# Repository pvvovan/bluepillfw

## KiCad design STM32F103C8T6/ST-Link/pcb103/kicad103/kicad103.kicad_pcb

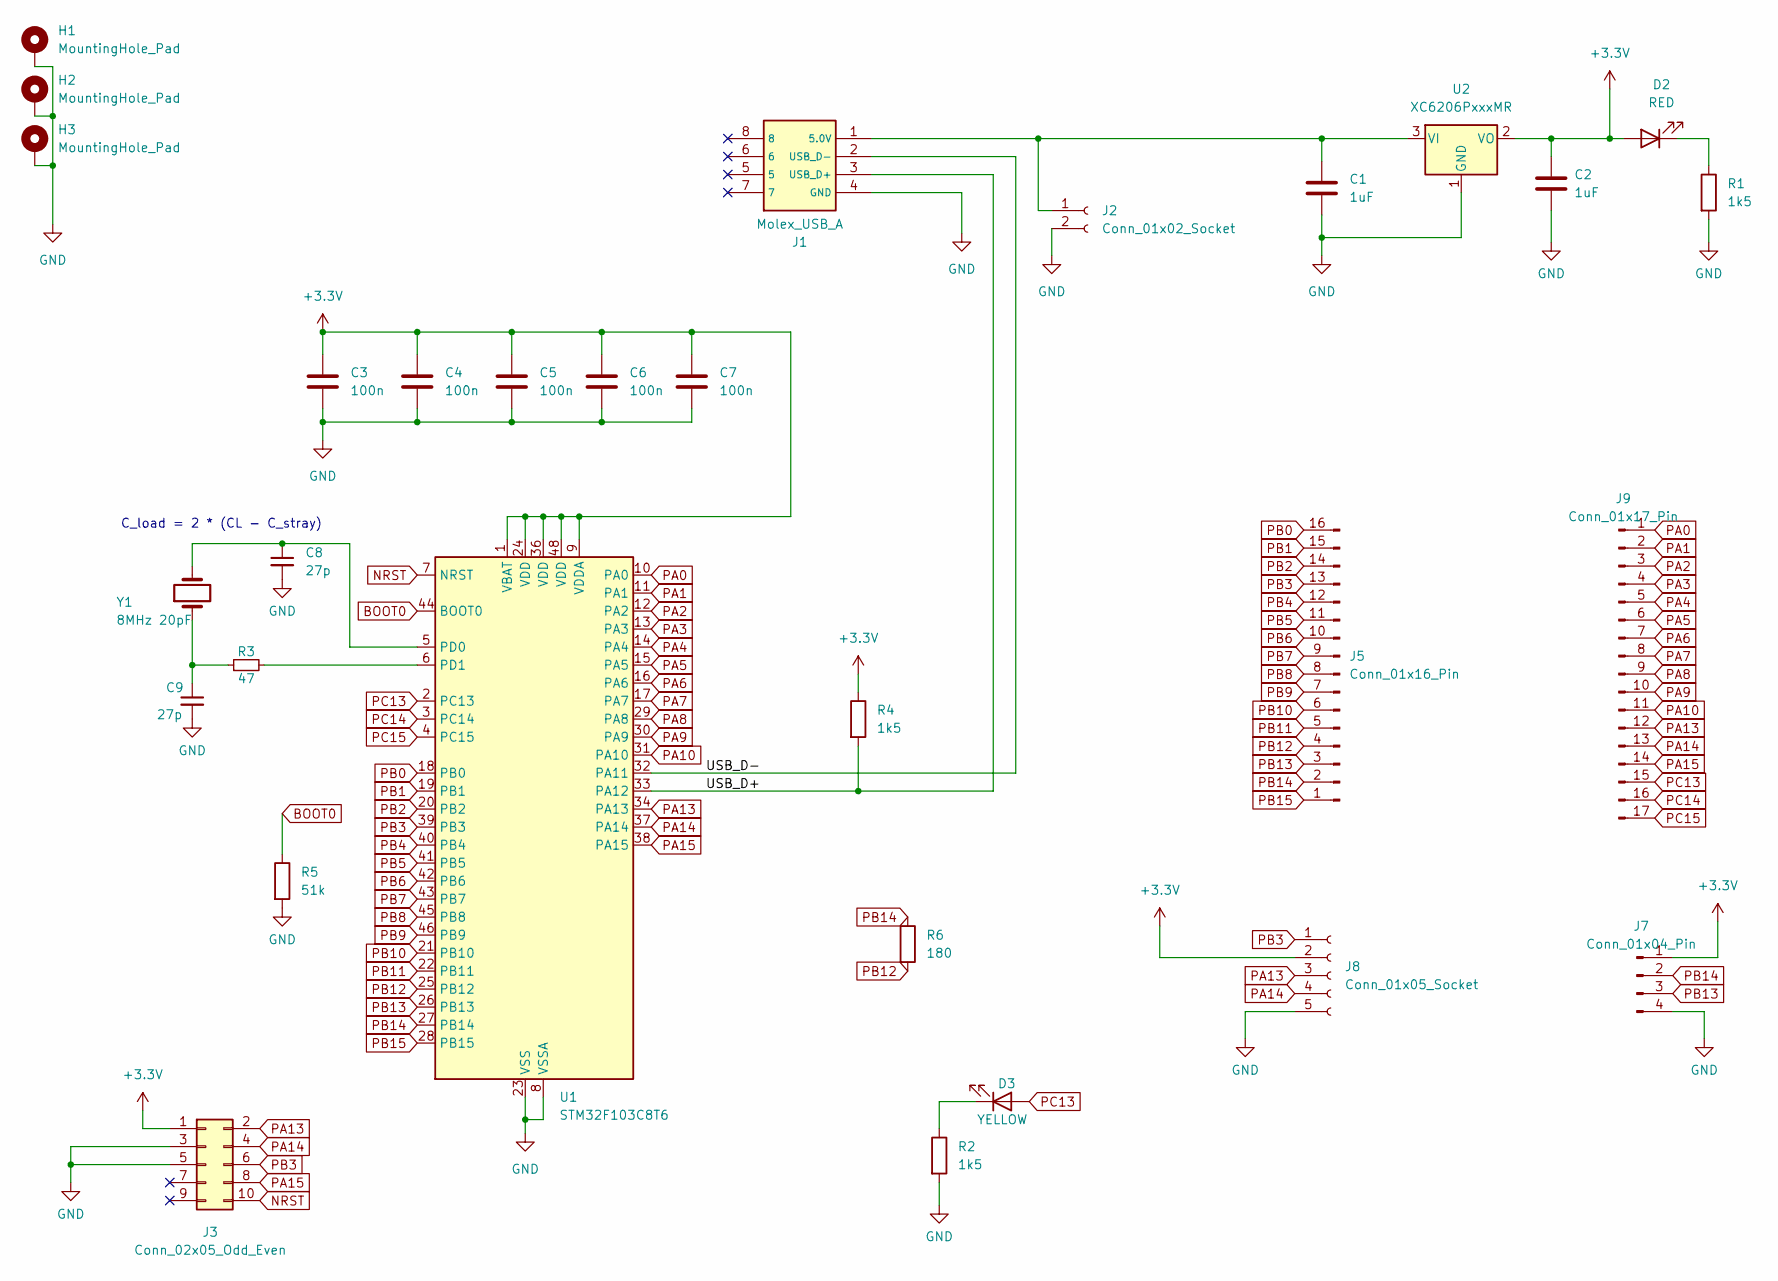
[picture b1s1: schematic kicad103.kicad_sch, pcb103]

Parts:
C1, C2: 1uF; C_0805_2012Metric; JLC # C28323
C3, C4, C5, C6, C7: 100n; C_0603_1608Metric; JLC # C14663
C8, C9: 27p; C_0402_1005Metric; JLC # C1557
D2: RED; LED_0805_2012Metric; JLC # C84256
D3: YELLOW; LED_0805_2012Metric; JLC # C2296
H1, H2, H3: MountingHole_Pad; MountingHole_4.3mm_M4_Pad_Via
J1: Molex_USB_A; Manufacturer_Part_Number 0480372200; Mouser Part Number N/A
J2: Conn_01x02_Socket; PinSocket_1x02_P2.54mm_Vertical
J3: Conn_02x05_Odd_Even; PinHeader_2x05_P1.27mm_Vertical_SMD; JLC # C2881910
J5: Conn_01x16_Pin; PinHeader_1x16_P2.54mm_Vertical
J7: Conn_01x04_Pin; PinSocket_1x04_P2.54mm_Vertical
J8: Conn_01x05_Socket; PinSocket_1x05_P2.54mm_Vertical
J9: Conn_01x17_Pin; PinHeader_1x17_P2.54mm_Vertical
R1, R2, R4: 1k5; R_0805_2012Metric; JLC # C4310
R3: 47; R_0402_1005Metric; JLC # C25118
R5: 51k; R_0805_2012Metric; JLC # C17737
R6: 180; R_1206_3216Metric; JLC # C17924
U1: STM32F103C8T6; LQFP-48_7x7mm_P0.5mm; JLC # C8734
U2: XC6206PxxxMR; SOT-23-3; JLC # C5446
Y1: 8MHz 20pF; Crystal_SMD_5032-2Pin_5.0x3.2mm; JLC # C115962

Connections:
+3.3V: C2.1, C3.1, C4.1, C5.1, C6.1, C7.1, D2.2 (A), J3.1, J7.1, J8.2, R4.1, U1.1 (VBAT), U1.9 (VDDA), U1.24 (VDD), U1.36 (VDD), U1.48 (VDD), U2.2 (VO)
/USB_D+: J1.3 (USB_D+), R4.2, U1.33 (PA12)
/USB_D-: J1.2 (USB_D-), U1.32 (PA11)
BOOT0: R5.1, U1.44 (BOOT0)
GND: C1.2, C2.2, C3.2, C4.2, C5.2, C6.2, C7.2, C8.2, C9.2, H1.1, H2.1, H3.1, J1.4 (GND), J2.2, J3.3, J3.5, J7.4, J8.5, R1.2, R2.2, R5.2, U1.8 (VSSA), U1.23 (VSS), U1.35 (VSS), U1.47 (VSS), U2.1 (GND)
NRST: J3.10, U1.7 (NRST)
unnamed: C9.1, R3.1, Y1.1
unnamed: D2.1 (K), R1.1
unnamed: D3.1 (K), R2.1
unnamed: C1.1, J1.1 (5.0V), J2.1, U2.3 (VI)
unnamed: C8.1, U1.5 (PD0), Y1.2
unnamed: R3.2, U1.6 (PD1)
PA0: J9.1, U1.10 (PA0)
PA1: J9.2, U1.11 (PA1)
PA2: J9.3, U1.12 (PA2)
PA3: J9.4, U1.13 (PA3)
PA4: J9.5, U1.14 (PA4)
PA5: J9.6, U1.15 (PA5)
PA6: J9.7, U1.16 (PA6)
PA7: J9.8, U1.17 (PA7)
PA8: J9.9, U1.29 (PA8)
PA9: J9.10, U1.30 (PA9)
PA10: J9.11, U1.31 (PA10)
PA13: J3.2, J8.3, J9.12, U1.34 (PA13)
PA14: J3.4, J8.4, J9.13, U1.37 (PA14)
PA15: J3.8, J9.14, U1.38 (PA15)
PB0: J5.16, U1.18 (PB0)
PB1: J5.15, U1.19 (PB1)
PB2: J5.14, U1.20 (PB2)
PB3: J3.6, J5.13, J8.1, U1.39 (PB3)
PB4: J5.12, U1.40 (PB4)
PB5: J5.11, U1.41 (PB5)
PB6: J5.10, U1.42 (PB6)
PB7: J5.9, U1.43 (PB7)
PB8: J5.8, U1.45 (PB8)
PB9: J5.7, U1.46 (PB9)
PB10: J5.6, U1.21 (PB10)
PB11: J5.5, U1.22 (PB11)
PB12: J5.4, R6.2, U1.25 (PB12)
PB13: J5.3, J7.3, U1.26 (PB13)
PB14: J5.2, J7.2, R6.1, U1.27 (PB14)
PB15: J5.1, U1.28 (PB15)
PC13: D3.2 (A), J9.15, U1.2 (PC13)
PC14: J9.16, U1.3 (PC14)
PC15: J9.17, U1.4 (PC15)

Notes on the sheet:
C_load = 2 * (CL - C_stray)

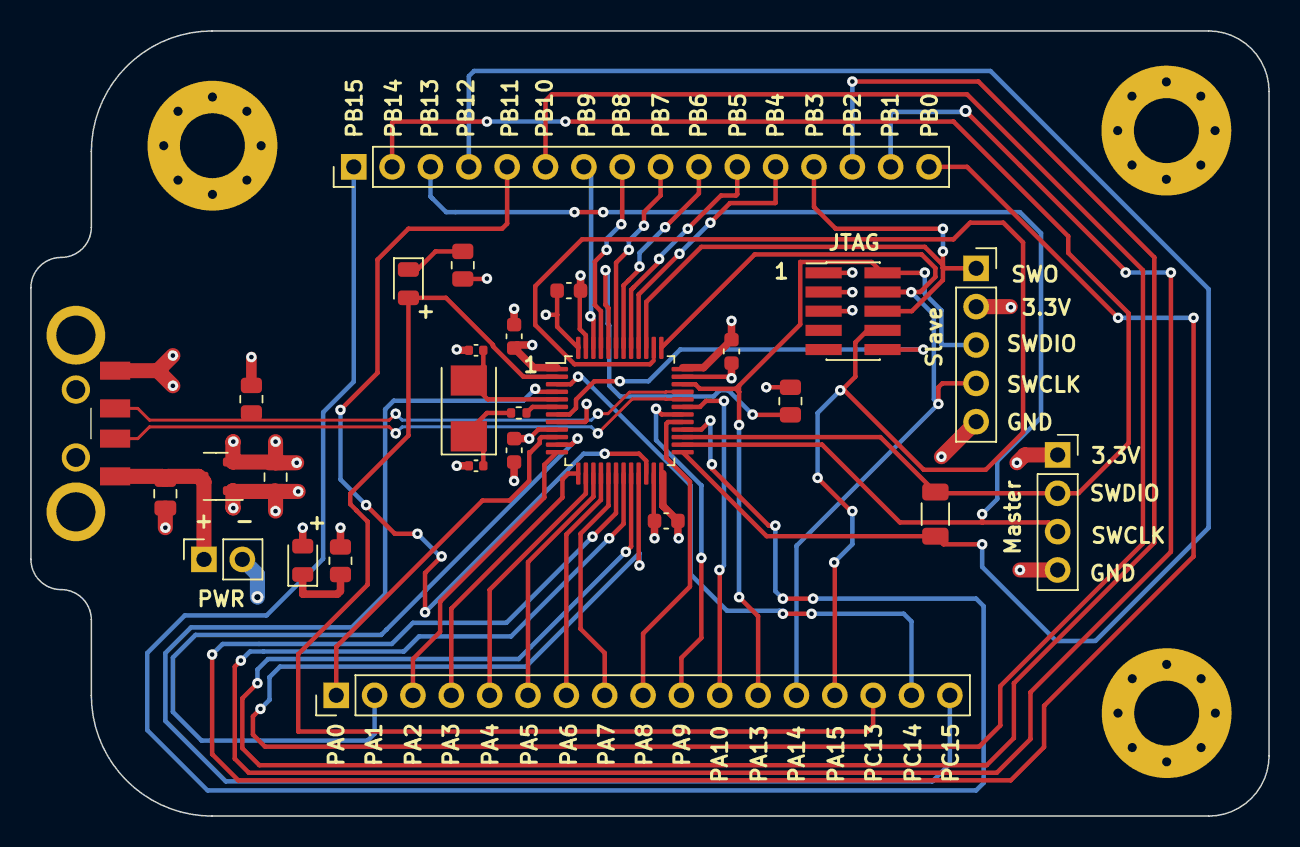
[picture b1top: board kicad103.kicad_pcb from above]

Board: 4 copper layers, 82.0 x 52.0 mm, 30 parts (0 on the bottom side), 45 nets.

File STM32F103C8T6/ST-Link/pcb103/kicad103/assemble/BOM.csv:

Comment,Designator,Footprint,JLCPCB Part#
1uF,"C1, C2",Capacitor_SMD:C_0805_2012Metric,C28323
100n,"C3, C4, C5, C6, C7",Capacitor_SMD:C_0603_1608Metric,C14663
27p,"C8, C9",Capacitor_SMD:C_0402_1005Metric,C1557
RED,D2,LED_SMD:LED_0805_2012Metric,C84256
YELLOW,D3,LED_SMD:LED_0805_2012Metric,C2296
Conn_02x05_Odd_Even,J3,Connector_PinHeader_1.27mm:PinHeader_2x05_P1.27mm_Vertical_SMD,C2881910
1k5,"R1, R2, R4",Resistor_SMD:R_0805_2012Metric,C4310
47,R3,Resistor_SMD:R_0402_1005Metric,C25118
51k,R5,Resistor_SMD:R_0805_2012Metric,C17737
180,R6,Resistor_SMD:R_1206_3216Metric,C17924
STM32F103C8T6,U1,Package_QFP:LQFP-48_7x7mm_P0.5mm,C8734
XC6206PxxxMR,U2,Package_TO_SOT_SMD:SOT-23-3,C5446
8MHz 20pF,Y1,Crystal:Crystal_SMD_5032-2Pin_5.0x3.2mm,C115962

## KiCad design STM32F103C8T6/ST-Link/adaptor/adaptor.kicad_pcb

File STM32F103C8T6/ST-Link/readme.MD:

# ST-Link v2.1

en.stsw-link007_V2-32-22.zip - firmvare update for Bootloader-2-1.bin

Bootloader-2-1.bin           - bootloader ST-Link v2.1

STLinkV2.J16.S4.bin          - ST-Link v2.0 J16.S4

wiring:

mini wiring:

st-flash --debug write STLinkV2.J16.S4.bin 0x8000000

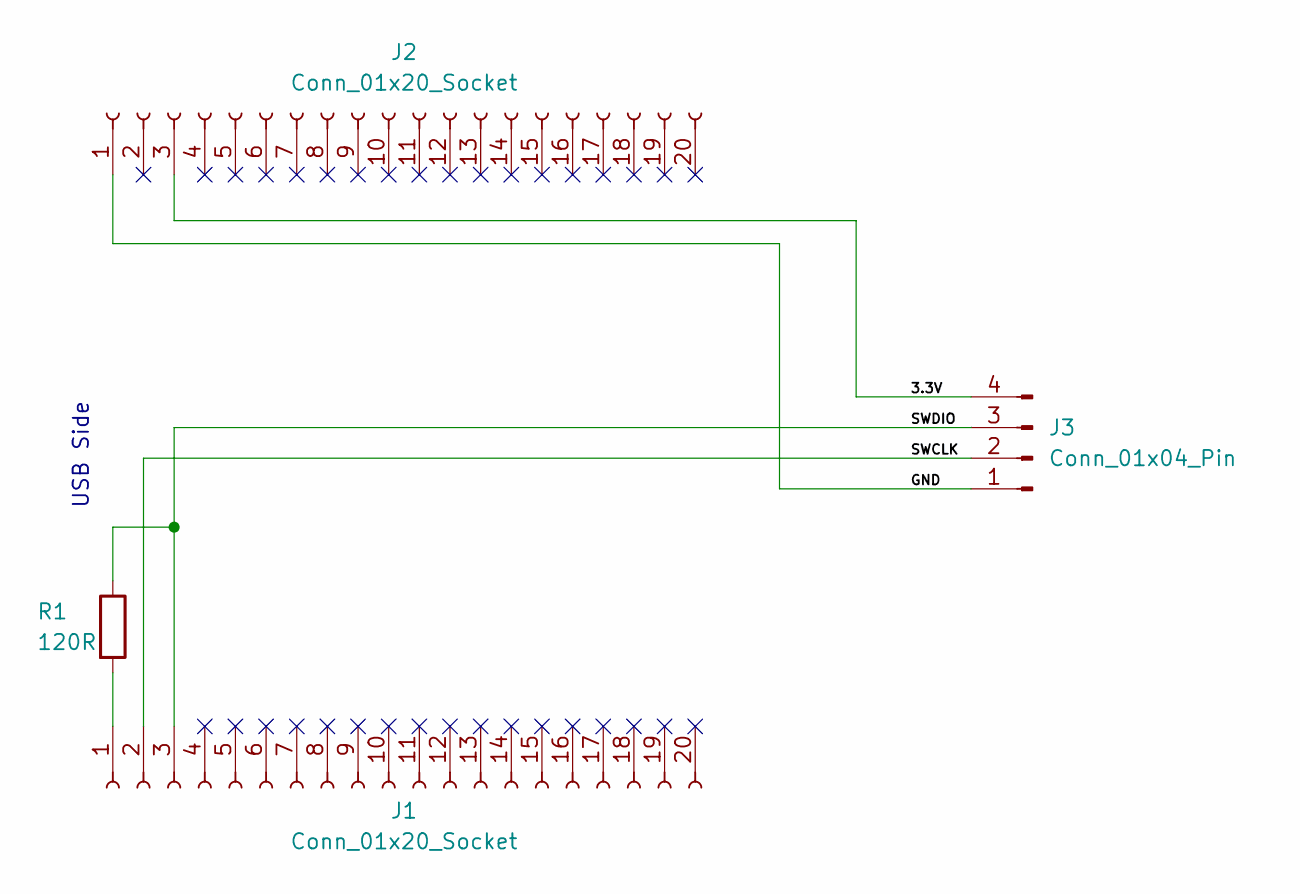
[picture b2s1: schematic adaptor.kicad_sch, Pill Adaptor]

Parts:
J1, J2: Conn_01x20_Socket; PinSocket_1x20_P2.54mm_Vertical
J3: Conn_01x04_Pin; PinSocket_1x04_P2.54mm_Vertical
R1: 120R; R_Axial_DIN0204_L3.6mm_D1.6mm_P5.08mm_Horizontal

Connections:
/3.3V: J2.3, J3.4
/GND: J2.1, J3.1
/SWCLK: J1.2, J3.2
/SWDIO: J1.3, J3.3, R1.1
unnamed: J1.1, R1.2

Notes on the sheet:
USB Side

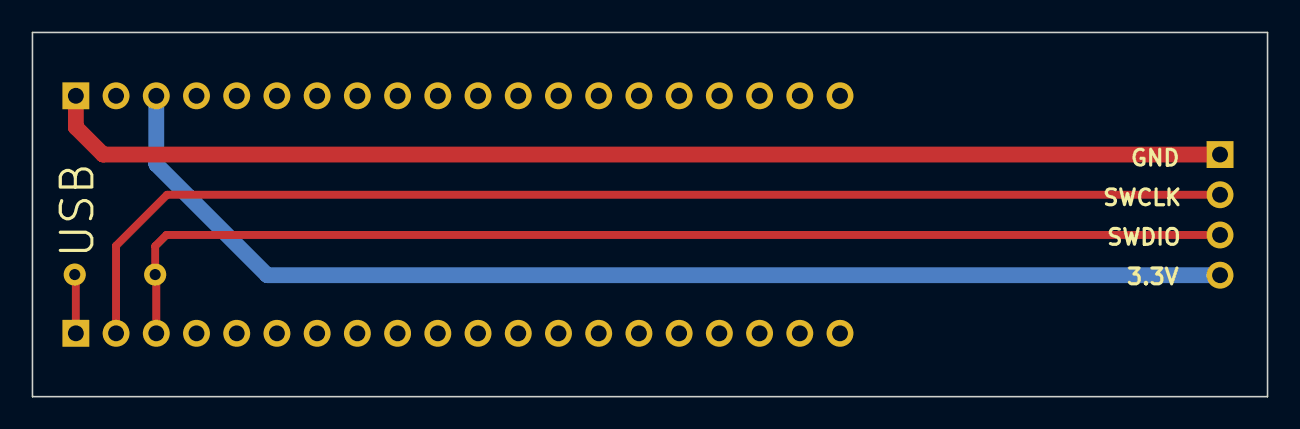
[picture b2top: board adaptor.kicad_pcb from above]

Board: 2 copper layers, 78.0 x 23.0 mm, 4 parts (0 on the bottom side), 5 nets.

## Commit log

2023-08-09 Add schematics
2023-08-13 Create schematics
2023-08-13 Place elements
2023-08-13 Edit footprint
2023-08-13 Generate gerber files
2023-08-26 SWD socket connector
2023-08-26 remove gerbers
2023-08-26 Space for SWD connector
2023-08-27 Remove silk lines
2023-08-27 Update stlink version
2023-08-27 Remove empty firmware
2023-09-17 Create pcb103
2023-09-18 Add USB Type A
2023-09-18 Add parts
2023-09-18 Add 3.3V LDO
2023-09-18 Add 3.3V power capacitors
2023-09-18 Add power header
2023-09-18 Add power LED
2023-09-18 Add status LED
2023-09-18 Add 8MHz crystal
2023-09-18 Pull-up resistor on USB_DP line
2023-09-18 Add JTAG
2023-09-18 Remaining pins
2023-09-18 SWO/SWD
2023-09-18 SWD 220R
2023-09-18 Mounting holes
2023-09-18 Fix power lines
2023-09-18 USB differential pair
2023-09-18 Connect Debug
2023-09-18 Connect all
2023-09-19 Connect missing GND
2023-09-19 Remove unconnected line
2023-09-19 Fix USB footprint
2023-09-19 Fix min clearance
2023-09-19 Remove text label warnings
2023-09-19 Fix min drill hole size
2023-09-19 Fix min Pad to Pad clearance
2023-09-19 Fix remaining
2023-09-19 Move line from top header
2023-09-19 Move out bottom lines
2023-09-19 Move out mounting hole
2023-09-19 Clean lines from header pins
2023-09-19 Add header 1 front lables
2023-09-19 Add header 1 back lables
2023-09-19 Move crystal resistor
2023-09-19 Add header 2 front labels
2023-09-19 Add header 2 back labels
2023-09-19 Remove silkscreen lines
2023-09-19 Remove back silkscreen lines
2023-09-19 Generate footprint position file
2023-09-19 Generate BOM
2023-09-19 Draft order
2023-09-19 Update capabilities
2023-09-19 Move all elements to front side
2023-09-19 Fix warnings
2023-09-19 Generate gerber
2023-09-19 Create positioning files
2023-09-19 Update POS file
2023-09-20 Replace 3.3V regulator
2023-09-20 Create BOM
2023-09-20 Route voltage regulator
2023-09-20 Update footprints from library
2023-09-20 Update USB 3D model
2023-09-20 Reupdate USB 3D model
2023-09-20 Generate output files
2023-09-20 Remove unused backups
2023-09-20 Ordered
2023-09-20 Update USB 3D in library
2023-09-22 Add 3D readme pictures
2023-09-22 Move README as md file
2023-09-22 Add schematic
2023-09-22 Add mylib
2023-09-22 Add USB footprint
2023-09-22 Update USBA pin order
2023-09-22 Remove unused libs
2023-09-22 Update PCB tracks based on MyLib
2023-09-22 Fix ingnored
